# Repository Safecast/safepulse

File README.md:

# SafePulse

An open-source high-voltage power supply (HVPS) and pulse counter designed for Geiger tubes. The Safepulse is utilized in the newest version of Safecast devices, the [bGeigieZen](https://bgeigiezen.safecast.jp) and can be bough directly at [https://bgeigiezen.safecast.jp/store-2/safepulse/](https://bgeigiezen.safecast.jp/store-2/safepulse/)

---

## Table of Contents

- [Overview](#overview)
- [History](#history)
- [Features](#features)
- [Getting Started](#getting-started)
  - [Prerequisites](#prerequisites)
  - [Installation](#installation)
- [Documentation](#documentation)
- [Contributing](#contributing)
- [Issues and Support](#issues-and-support)
- [License](#license)

---

## Overview

SafePulse is a project aimed at creating a fully open-source high-voltage power supply that is compact, efficient, and reliable. Designed specifically for Geiger counters, it facilitates accurate radiation detection and measurement.

---

## History

The SafePulse journey began with Safecast's need for a high-performance HVPS that exceeded existing market solutions. Dan Sythe of International Medcom played a pivotal role in guiding the development process, providing components like the iRover—a commercial-grade miniature HVPS recognized by the IAEA.

While the iRover set a benchmark for reliability and performance, SafePulse was developed to customize its needs to the varying requirements of numerous Safecast device types. Using an open-source design based on a HEX CMOS inverter oscillator, MOSFET switch, and Cockroft-Walton multiplier, the initial design achieved low power consumption (80 µA). However, challenges such as double pulses to the CPU and high count rate predictability led to refinements, including adding a multivibrator for fixed pulse widths. SafePulse is as much a reference design as a specific product, as variants of the core SafePulse design already feature a high-speed nano-amp I2C counter as well as alternative packagings.

SafePulse evolved into a compact 4-layer design to meet size constraints while ensuring consistent performance across component substitutions.

---

## Features

- **Open-Source Design**: All design files and source code are publicly available for modification.
- **High Performance**: Provides reliable high-voltage output tailored for Geiger tubes.
- **Compact and Efficient**: Space-saving design with minimal power consumption.

---

## Getting Started

### Prerequisites

To work with SafePulse, ensure you have the following tools and components:

- [KiCad](https://www.kicad.org/): Open-source electronic design automation software.
- Electronic components listed in the project's bill of materials (BOM).

### Installation

1. **Clone the Repository**:
```

git clone https://github.com/Safecast/safepulse.git

```

2. **Open with KiCad**:
- Launch KiCad.
- Open the `SafePulse.kicad_pro` project file from the cloned repository.

3. **Review and Modify**:
- Access schematics and PCB layouts.
- Make desired modifications or improvements.

---

## Documentation

Detailed schematics and design documents are available in the repository. Refer to the [SafePulse.pdf](https://github.com/Safecast/safepulse/blob/main/SafePulse.pdf) file for comprehensive information.

---

## Contributing

Contributions are welcome! Follow these steps:

1. Fork the repository.
2. Create a new branch for your feature or bug fix:
```

git checkout -b feature-name

```
3. Commit your changes:
```

git commit -m "Add feature"

```
4. Push to your forked repository:
```

git push origin feature-name

```
5. Submit a pull request detailing your changes.

Please ensure contributions align with project objectives and coding standards.

---

## Issues and Support

For issues or questions, visit the [GitHub Issues](https://github.com/Safecast/safepulse/issues) section of the repository.

---

## License

This project is licensed under the MIT License. You are free to use, modify, and distribute this software under its terms.
```

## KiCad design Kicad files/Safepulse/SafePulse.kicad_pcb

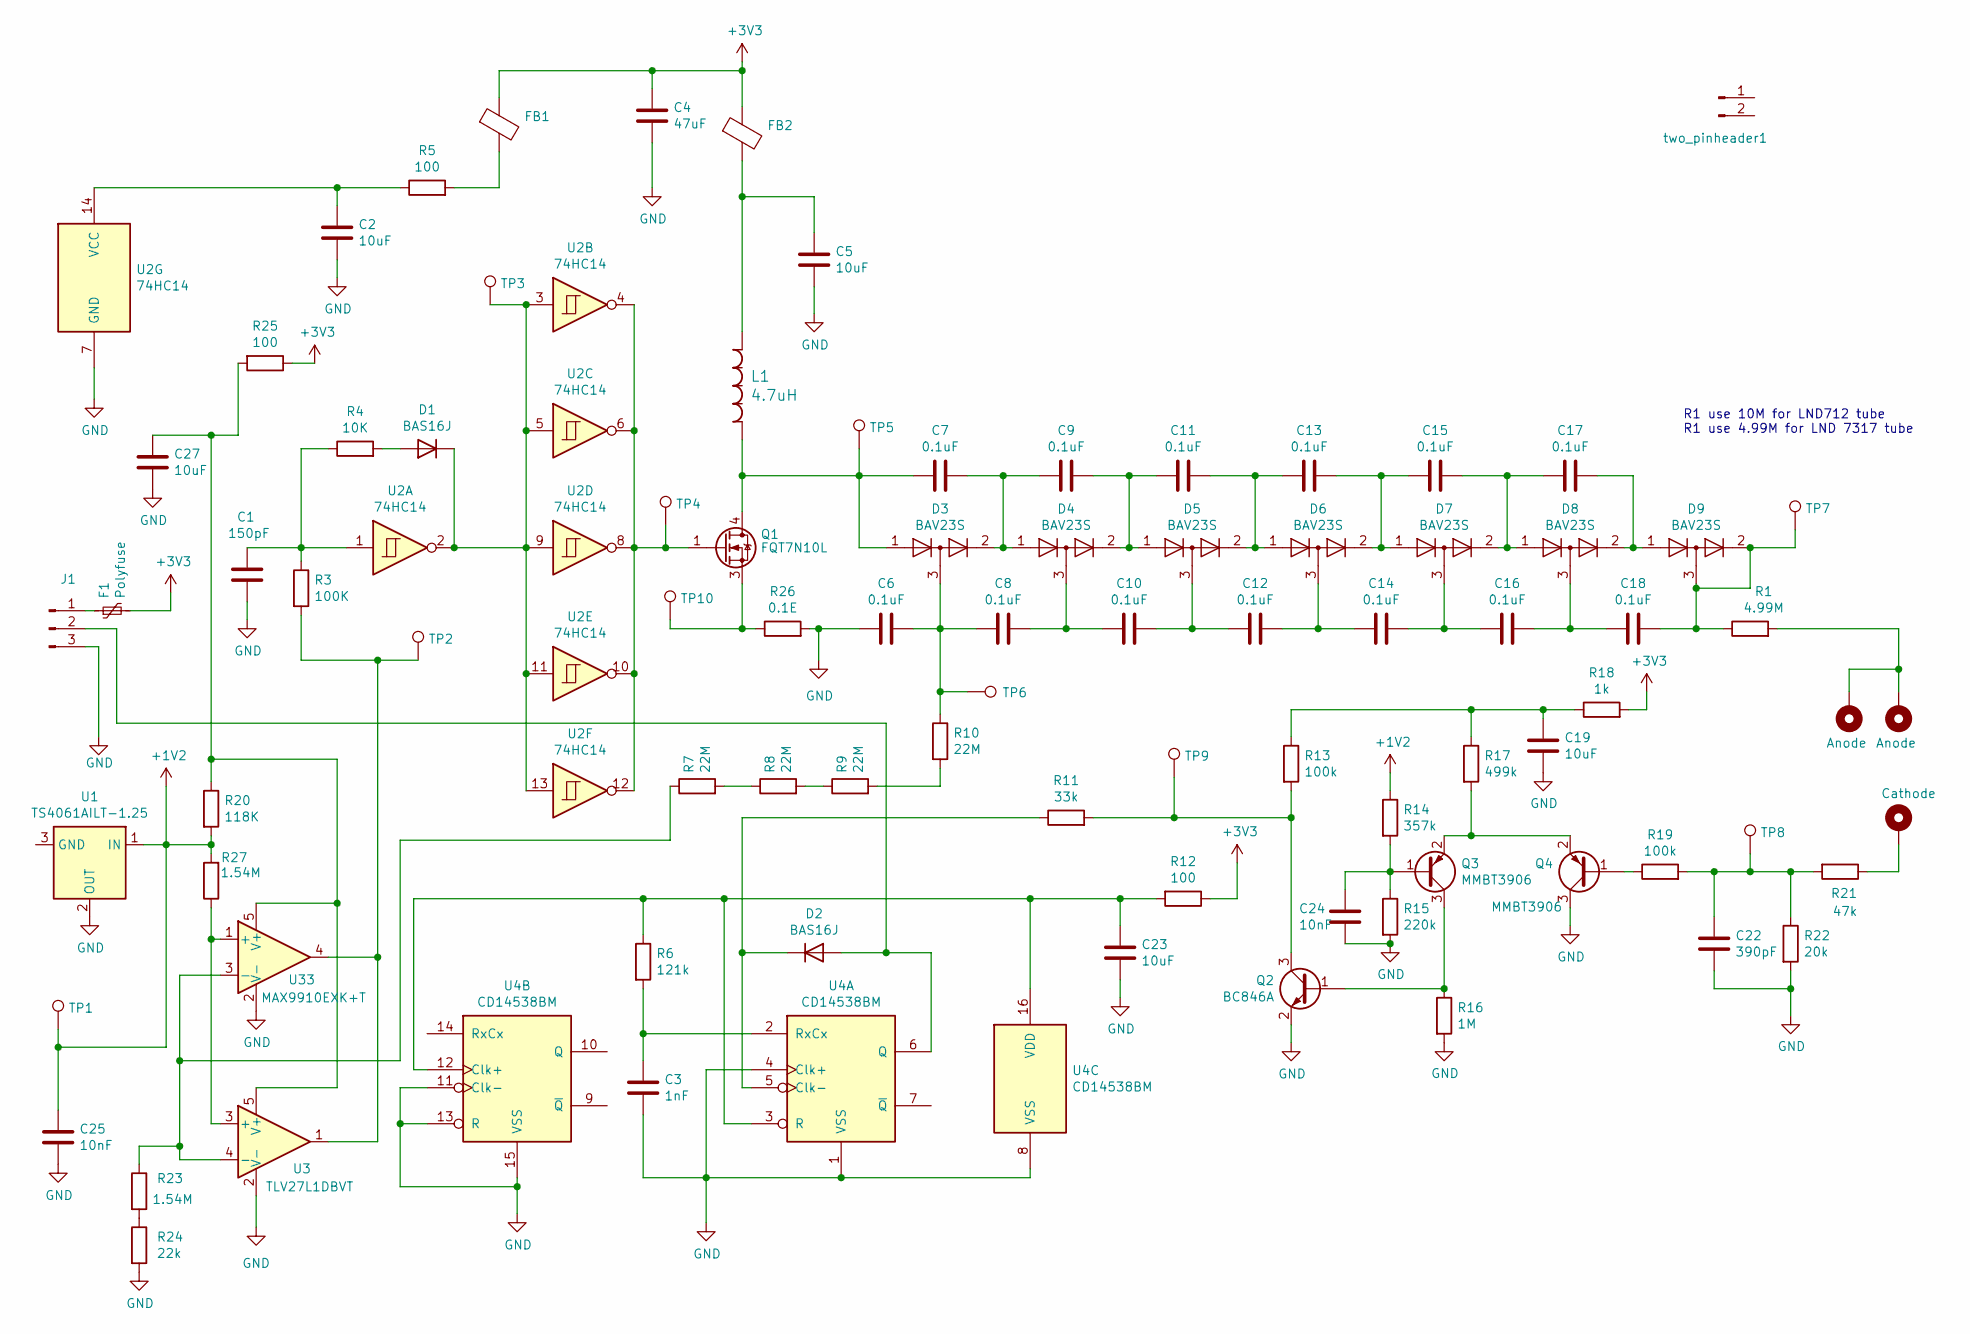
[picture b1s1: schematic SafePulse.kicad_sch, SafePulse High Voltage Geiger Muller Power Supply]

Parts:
C1: 150pF; C_0805_2012Metric; Digikey 732-12190-1-ND
C2, C5, C19, C23, C27: 10uF; C_0805_2012Metric; Digikey 1276-6455-1-ND
C3: 1nF; C_0805_2012Metric; Digikey 478-1371-1-ND
C4: 47uF; C_1210_3225Metric; Digikey 587-5425-1-ND
C6, C7, C8, C9, C10, C11, C12, C13, C14, C15, C16, C17, C18: 0.1uF; C_0805_2012Metric; Digikey 445-6808-1-ND
C22: 390pF; C_0805_2012Metric; Digikey 399-1132-1-ND
C24, C25: 10nF; C_0805_2012Metric; Digikey 1276-1015-1-ND
D1, D2: BAS16J; D_SOD-323; Digikey 1727-4797-1-ND
D3, D4, D5, D6, D7, D8, D9: BAV23S; SOT-23; Digikey BAV23SFSCT-ND
F1: Polyfuse; R_0805_2012Metric; Digikey 490-8510-1-ND
FB1, FB2: 74279220321; R_0805_2012Metric; Digikey 732-6125-1-ND
H1: Cathode; TestPoint_Loop_D2.60mm_Drill1.4mm_Beaded
H2, H4: Anode; TestPoint_Loop_D3.50mm_Drill1.4mm_Beaded
J1: Conn_01x03_Male; PinHeader_1x03_P2.54mm_Vertical
L1: 4.7uH; L_Taiyo-Yuden_MD-4040; Digikey 587-4451-1-ND
Q1: FQT7N10L; SOT-223-3_TabPin4; Digikey FQT7N10LTFCT-ND
Q2: BC846A; SOT-23; Digikey BC846A-7FDICT-ND
Q3, Q4: MMBT3906; SOT-23; Digikey MMBT3906LT1GOSCT-ND
R1: 4.99M; R_1206_3216Metric; Digikey RHM4.99MAICT-ND
R3: 100K; R_0805_2012Metric; Digikey RMCF0805FT100KCT-ND
R4: 10K; R_0805_2012Metric; Digikey RNCP0805FTD10K0CT-ND
R5: 100; R_0805_2012Metric; LCSC Part # C328380
R6: 121k; R_0805_2012Metric; Digikey 2019-RK73H2ATTD1213FCT-ND
R7, R8, R9, R10: 22M; R_0805_2012Metric; Digikey RMCF0805FT22M0CT-ND
R11: 33k; R_0805_2012Metric; Digikey A129767CT-ND
R12, R25: 100; R_0805_2012Metric; Digikey A106053CT-ND
R13, R19: 100k; R_0805_2012Metric; Digikey RMCF0805FT100KCT-ND
R14: 357k; R_0805_2012Metric; Digikey 2019-RK73H2ATTD3573FCT-ND
R15: 220k; R_0805_2012Metric; Digikey CR0805-FX-2203ELFCT-ND
R16: 1M; R_0805_2012Metric; Digikey YAG3361CT-ND
R17: 499k; R_0805_2012Metric; Digikey RMCF0805FT499KCT-ND
R18: 1k; R_0805_2012Metric; Digikey RNCP0805FTD1K00CT-ND
R20: 118K; R_0805_2012Metric; Digikey 311-118KCRCT-ND
R21: 47k; R_0805_2012Metric; Digikey 311-47.0KCRCT-ND
R22: 20k; R_0805_2012Metric; Digikey RMCF0805FT20K0CT-ND
R23, R27: 1.54M; R_0805_2012Metric; Digikey 311-1.54MCRCT-ND
R24: 22k; R_0805_2012Metric; Digikey CR0805-FX-2202ELFCT-ND
R26: 0.1E; R_0805_2012Metric; Digikey 408-1556-1-ND
TP1, TP2, TP3, TP4, TP5, TP6, TP7, TP8, TP9, TP10: TestPoint; TestPoint_Pad_1.0x1.0mm
U1: TS4061AILT-1.25; SOT-23; Digikey 497-15222-1-ND
U2: 74HC14; SOIC-14_3.9x8.7mm_P1.27mm; LCSC Part # C232776
U3: TLV27L1DBVT; SOT-23-5; Digikey 296-26814-1-ND
U4: CD14538BM; SOIC-16_3.9x9.9mm_P1.27mm; Digikey 296-32849-5-ND
U33: MAX9910EXK+T; SOT-353_SC-70-5; Digikey MAX9910EXK+TCT-ND
two_pinheader1: Conn_01x03_Male; PinHeader_1x02_P2.54mm_Vertical

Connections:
+1V2: C25.1, R14.1, R20.2, R27.2, TP1.1, U1.1 (IN)
+3V3: C4.1, F1.2, FB1.1, FB2.1, R12.1, R18.2, R25.1
GND: C1.2, C2.2, C3.2, C4.2, C5.2, C6.1, C19.2, C22.2, C23.2, C24.2, C25.2, C27.2, J1.3, Q2.2 (E), Q4.3 (C), R15.2, R16.2, R22.2, R24.2, R26.2, U1.2 (OUT), U2.7 (GND), U3.2 (V-), U4.1 (VSS), U4.4 (Clk+), U4.8 (VSS), U4.11 (Clk-), U4.13 (R), U4.15 (VSS), U33.2 (V-)
unnamed: C1.1, R3.1, R4.1, U2.1
unnamed: C5.1, FB2.2, L1.1
unnamed: C6.2, C8.1, D3.3 (K), R10.1, TP6.1
unnamed: C8.2, C10.1, D4.3 (K)
unnamed: C10.2, C12.1, D5.3 (K)
unnamed: C12.2, C14.1, D6.3 (K)
unnamed: C14.2, C16.1, D7.3 (K)
unnamed: C16.2, C18.1, D8.3 (K)
unnamed: C19.1, R13.1, R17.1, R18.1
unnamed: C22.1, R19.2, R21.2, R22.1, TP8.1
unnamed: D1.2 (A), R4.2
unnamed: D1.1 (K), TP3.1, U2.2, U2.3, U2.5, U2.9, U2.11, U2.13
unnamed: D2.2 (A), J1.2, U4.6 (Q)
unnamed: D2.1 (K), R11.1, U4.5 (Clk-)
unnamed: C7.2, C9.1, D3.2 (A), D4.1 (K)
unnamed: C9.2, C11.1, D4.2 (A), D5.1 (K)
unnamed: C11.2, C13.1, D5.2 (A), D6.1 (K)
unnamed: C13.2, C15.1, D6.2 (A), D7.1 (K)
unnamed: C15.2, C17.1, D7.2 (A), D8.1 (K)
unnamed: C17.2, D8.2 (A), D9.1 (K)
unnamed: C18.2, D9.2 (A), D9.3 (K), R1.1, TP7.1
unnamed: FB1.2, R5.2
unnamed: H1.1, R21.1
unnamed: H2.1, H4.1, R1.2
unnamed: F1.1, J1.1
unnamed: C7.1, D3.1 (K), L1.2, Q1.4 (D), TP5.1
unnamed: Q1.1 (G), TP4.1, U2.4, U2.6, U2.8, U2.10, U2.12
unnamed: Q1.3 (S), R26.1, TP10.1
unnamed: Q2.1 (B), Q3.3 (C), R16.1
unnamed: Q2.3 (C), R11.2, R13.2, TP9.1
unnamed: C24.1, Q3.1 (B), R14.2, R15.1
unnamed: Q3.2 (E), Q4.2 (E), R17.2
unnamed: Q4.1 (B), R19.1
unnamed: R3.2, TP2.1, U3.1, U33.4
unnamed: R7.2, R8.1
unnamed: R8.2, R9.1
unnamed: R9.2, R10.2
unnamed: R23.2, R24.1
unnamed: C2.1, R5.1, U2.14 (VCC)
unnamed: R27.1, U3.3 (+), U33.1 (+)
unnamed: R7.1, R23.1, U3.4 (-), U33.3 (-)
unnamed: C27.1, R20.1, R25.2, U3.5 (V+), U33.5 (V+)
unnamed: C23.1, R6.1, R12.2, U4.3 (R), U4.12 (Clk+), U4.16 (VDD)
unnamed: C3.1, R6.2, U4.2 (RxCx)

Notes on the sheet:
R1 use 10M for LND712 tube R1 use 4.99M for LND 7317 tube

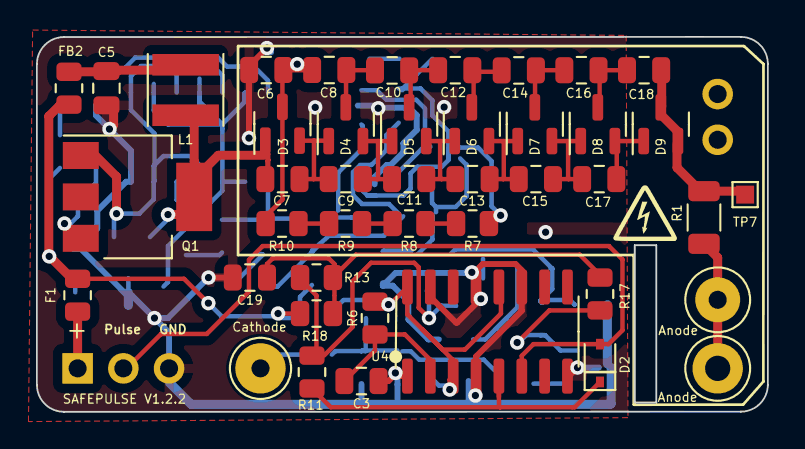
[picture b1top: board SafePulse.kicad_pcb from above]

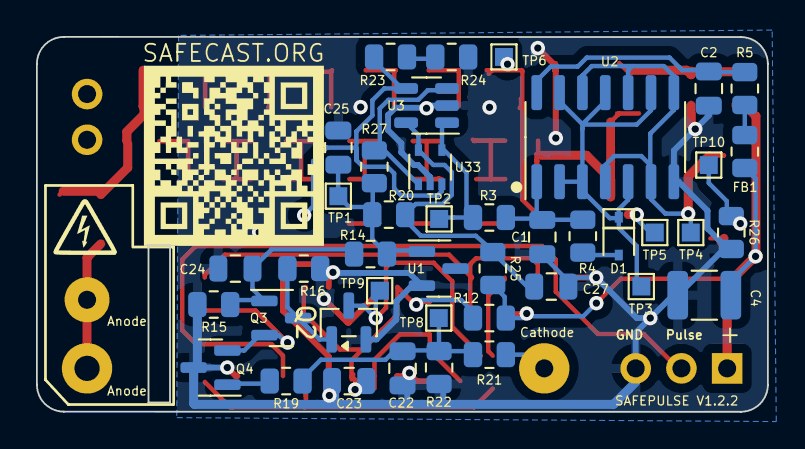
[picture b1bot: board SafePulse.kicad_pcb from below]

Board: 4 copper layers, 40.6 x 20.8 mm, 89 parts (43 on the bottom side), 47 nets.

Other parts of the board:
G2, G3: LOGO; HV warning

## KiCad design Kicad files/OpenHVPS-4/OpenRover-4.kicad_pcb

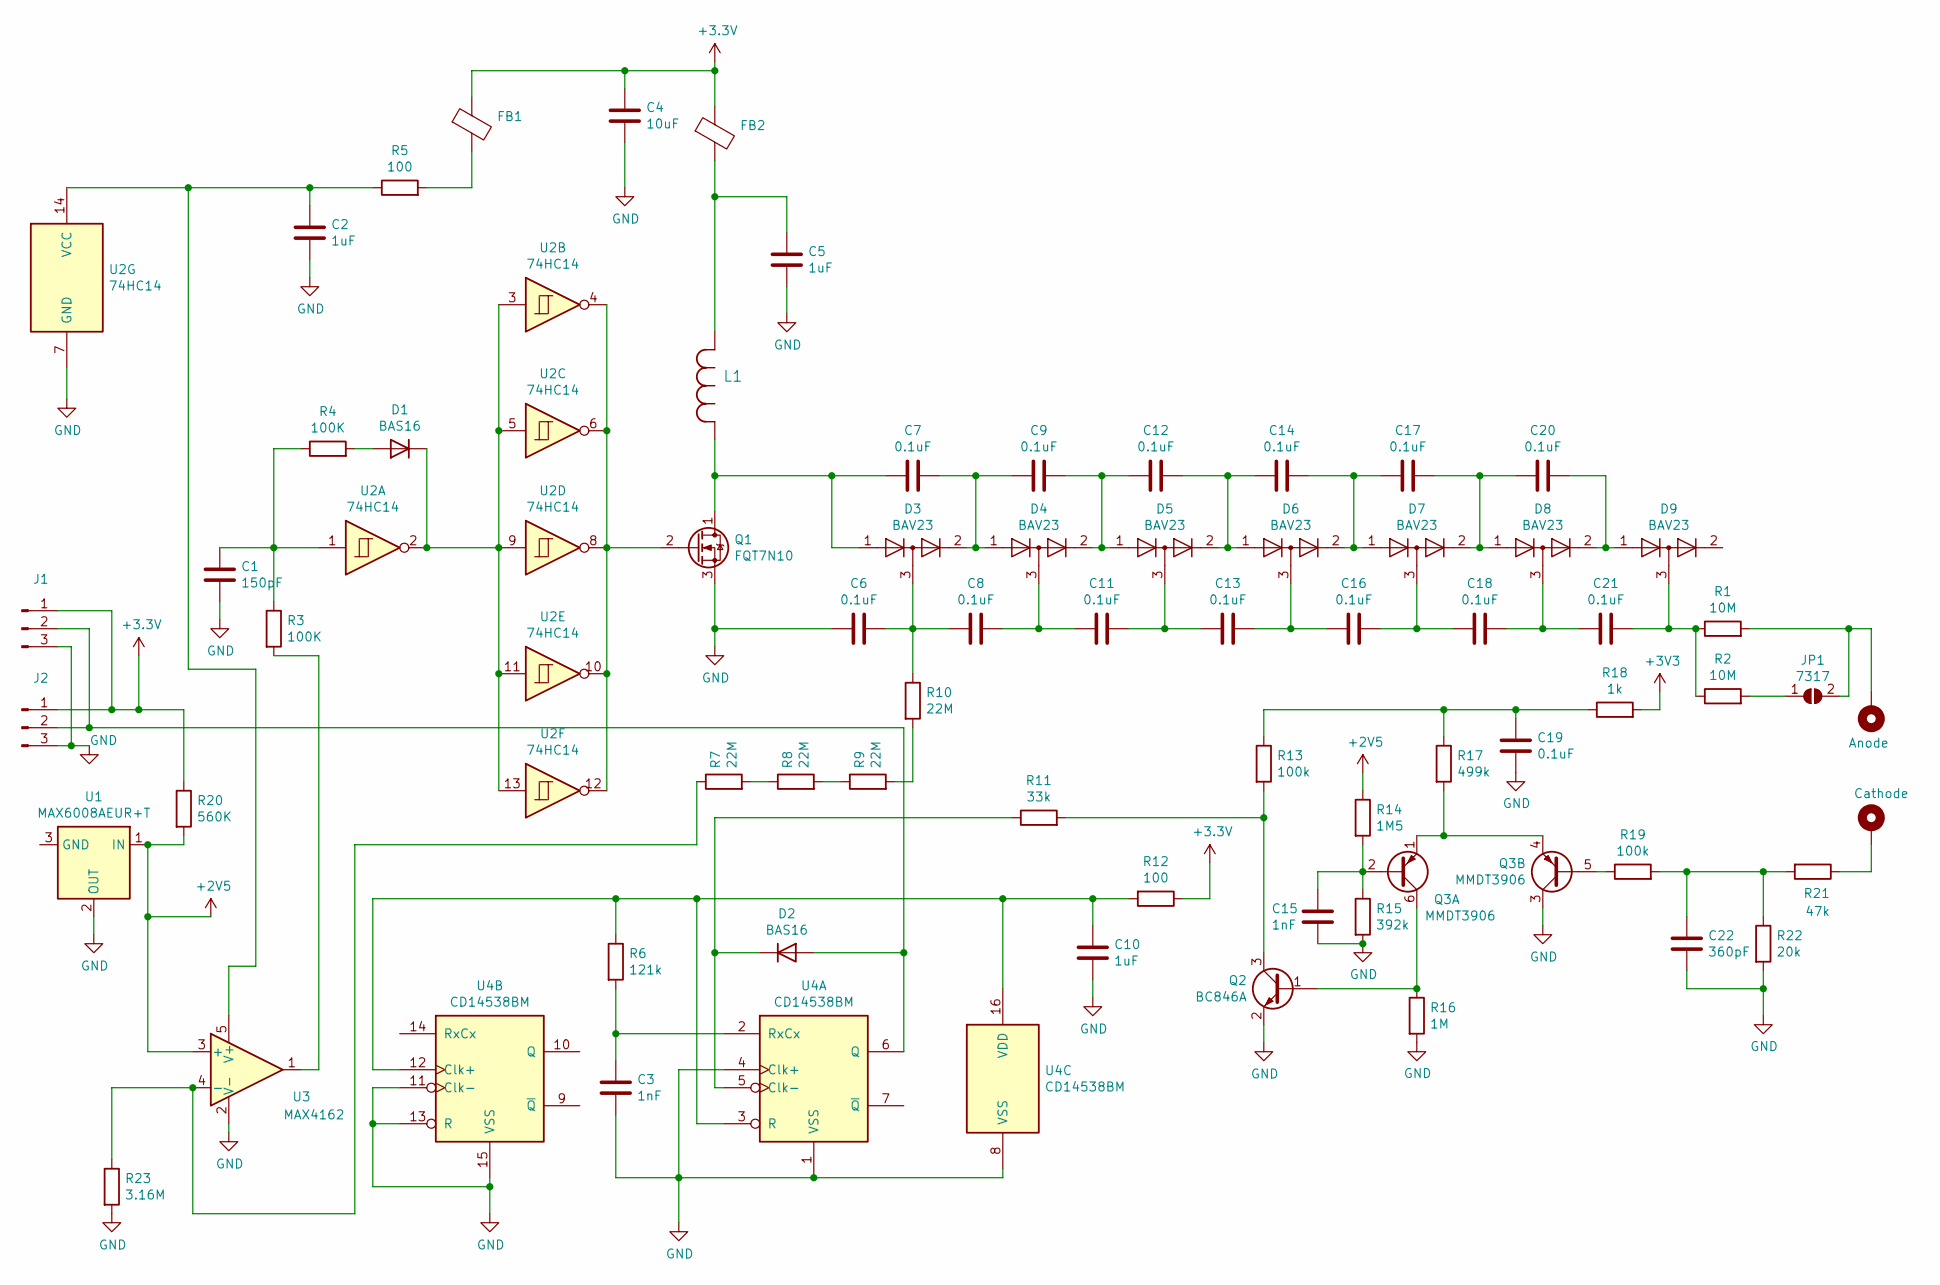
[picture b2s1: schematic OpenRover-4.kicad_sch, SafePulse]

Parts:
C1: 150pF; C_0805_2012Metric
C2, C5, C10: 1uF; C_0805_2012Metric
C3, C15: 1nF; C_0805_2012Metric
C4: 10uF; C_1210_3225Metric
C6, C7, C8, C9, C11, C12, C13, C14, C16, C17, C18, C19, C20, C21: 0.1uF; C_0805_2012Metric
C22: 360pF; C_0805_2012Metric
D1, D2: BAS16; D_SOT-23_ANK
D3, D4, D5, D6, D7, D8, D9: BAV23; SOT-23
FB1, FB2: BKP2125HS221-T; R_0805_2012Metric
H1: Cathode; TestPoint_Loop_D3.80mm_Drill2.0mm
H2: Anode; TestPoint_Loop_D3.80mm_Drill2.0mm
J1, J2: Conn_01x03_Male; PinHeader_1x03_P2.54mm_Vertical
JP1: 7317; SolderJumper-2_P1.3mm_Open_RoundedPad1.0x1.5mm
L1: NRS6020T2R2NMGJ; L_Taiyo-Yuden_MD-4040
Q1: FQT7N10; SOT-223-3_TabPin2
Q2: BC846A; SOT-23
Q3: MMDT3906; SOT-363_SC-70-6
R1, R2: 10M; R_1206_3216Metric
R3, R4: 100K; R_0805_2012Metric
R5, R12: 100; R_0805_2012Metric
R6: 121k; R_0805_2012Metric
R7, R8, R9, R10: 22M; R_0805_2012Metric
R11: 33k; R_0805_2012Metric
R13, R19: 100k; R_0805_2012Metric
R14: 1M5; R_0805_2012Metric
R15: 392k; R_0805_2012Metric
R16: 1M; R_0805_2012Metric
R17: 499k; R_0805_2012Metric
R18: 1k; R_0805_2012Metric
R20: 560K; R_0805_2012Metric
R21: 47k; R_0805_2012Metric
R22: 20k; R_0805_2012Metric
R23: 3.16M; R_0805_2012Metric
U1: MAX6008AEUR+T; SOT-23
U2: 74HC14; SOIC-14_3.9x8.7mm_P1.27mm
U3: MAX4162; SOT-23-5
U4: CD14538BM; SOIC-16_3.9x9.9mm_P1.27mm

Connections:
+2V5: R14.1, R20.2, U1.1 (IN), U3.3 (+)
GND: C1.2, C2.2, C3.2, C4.2, C5.2, C6.1, C10.2, C15.2, C19.2, C22.2, J1.3, J2.3, Q1.3 (S), Q2.2 (E), Q3.3 (C2), R15.2, R16.2, R22.2, R23.2, U1.2 (OUT), U2.7 (GND), U3.2 (V-), U4.1 (VSS), U4.4 (Clk+), U4.8 (VSS), U4.11 (Clk-), U4.13 (R), U4.15 (VSS)
unnamed: C1.1, R3.1, R4.1, U2.1
unnamed: C2.1, R5.1, U2.14 (VCC), U3.5 (V+)
unnamed: C3.1, R6.2, U4.2 (RxCx)
unnamed: C5.1, FB2.2, L1.1
unnamed: C6.2, C8.1, D3.3 (K), R10.1
unnamed: C7.1, D3.1 (K), L1.2, Q1.1 (D)
unnamed: C7.2, C9.1, D3.2 (A), D4.1 (K)
unnamed: C10.1, R6.1, R12.2, U4.3 (R), U4.12 (Clk+), U4.16 (VDD)
unnamed: C8.2, C11.1, D4.3 (K)
unnamed: C11.2, C13.1, D5.3 (K)
unnamed: C9.2, C12.1, D4.2 (A), D5.1 (K)
unnamed: C12.2, C14.1, D5.2 (A), D6.1 (K)
unnamed: C13.2, C16.1, D6.3 (K)
unnamed: C14.2, C17.1, D6.2 (A), D7.1 (K)
unnamed: C15.1, Q3.2 (B1), R14.2, R15.1
unnamed: C16.2, C18.1, D7.3 (K)
unnamed: C17.2, C20.1, D7.2 (A), D8.1 (K)
unnamed: C18.2, C21.1, D8.3 (K)
unnamed: C19.1, R13.1, R17.1, R18.1
unnamed: C20.2, D8.2 (A), D9.1 (K)
unnamed: C21.2, D9.3 (K), R1.1, R2.1
unnamed: C22.1, R19.2, R21.2, R22.1
unnamed: D1.1 (K), U2.2, U2.3, U2.5, U2.9, U2.11, U2.13
unnamed: D1.2 (A), R4.2
unnamed: D2.1 (K), R11.1, U4.5 (Clk-)
unnamed: D2.2 (A), J1.2, J2.2, U4.6 (Q)
unnamed: FB1.2, R5.2
unnamed: H1.1, R21.1
unnamed 30: H2.1, JP1.2 (B), R1.2; also elsewhere on the board
unnamed: JP1.1 (A), R2.2
unnamed: Q1.2 (G), U2.4, U2.6, U2.8, U2.10, U2.12
unnamed: Q2.1 (B), Q3.6 (C1), R16.1
unnamed: Q2.3 (C), R11.2, R13.2
unnamed: Q3.1 (E1), Q3.4 (E2), R17.2
unnamed: Q3.5 (B2), R19.1
unnamed: R3.2, U3.1
unnamed: R7.2, R8.1
unnamed: R8.2, R9.1
unnamed: R9.2, R10.2
unnamed: R7.1, R23.1, U3.4 (-)
no_connect_(D9-Pad2): D9.2 (A)
no_connect_(U1-Pad3): U1.3 (GND)
no_connect_(U4-Pad7): U4.7 (~Q)
no_connect_(U4-Pad9): U4.9 (~Q)
no_connect_(U4-Pad10): U4.10 (Q)
no_connect_(U4-Pad14): U4.14 (RxCx)

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
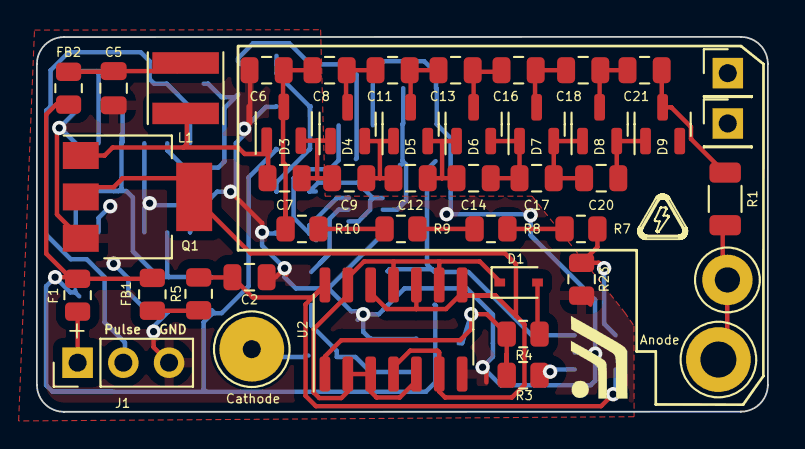
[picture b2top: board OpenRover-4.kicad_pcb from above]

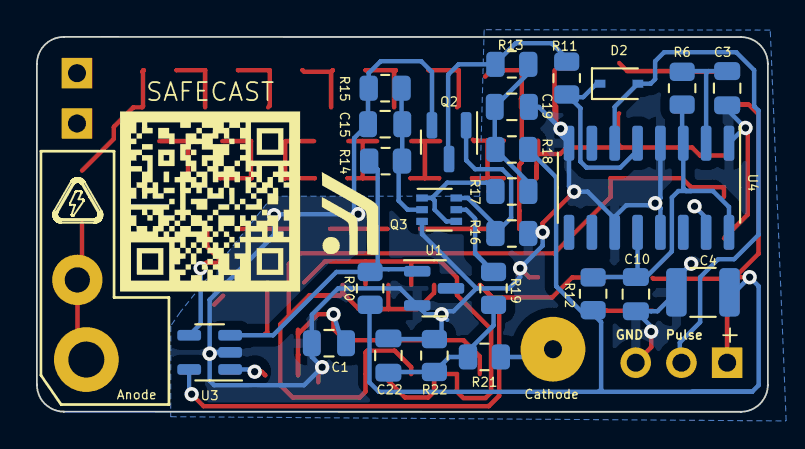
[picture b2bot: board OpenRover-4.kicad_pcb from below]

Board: 2 copper layers, 40.6 x 20.8 mm, 68 parts (26 on the bottom side), 43 nets.

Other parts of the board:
F1: Polyfuse; R_0805_2012Metric
H2#2: Anode; TestPoint_Loop_D3.80mm_Drill2.0mm

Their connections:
unnamed 30: H2#2.1; also elsewhere on the board

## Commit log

2021-01-09 Emply Kicad setup
2021-01-09 Added Irover 3D model files
2021-01-10 Updated with Allan his work.
2021-01-10 Modified read.me file
2021-01-10 Tested 74HC14 adding to the footprints
2021-01-10 Updated test for board sizes
2021-01-11 Add files via upload
    Finished front end.
2021-01-11 Updated the files from the allan zip files.
2021-01-11 Add files via upload
    Finished the Circuit Front End
2021-01-11 quick test parts layout/route and 3d models
2021-01-12 Renamed the files for OpenHVPS
2021-01-12 Create LICENSE
2021-01-12 Updated board with fill areas
2021-01-12 Tested new layout board
2021-01-12 Round conners and less vias. Space around holes
2021-01-12 version 2 of the SafePulse
2021-01-13 Added extra outputs and A-C placement moved
2021-01-13 test from allan
2021-01-13 test 4
2021-01-13 t test Q
2021-01-13 test rob allan
2021-01-13 test 7
2021-01-13 test8
2021-01-13 test 9
2021-01-13 cd \Users\allan\OneDrive\Documents\OpenHVPS Please enter the commit message for your changes. Lines starting updated the long board design
2021-01-13 changes to anode and cathode plus some parts layout, not routed!
2021-01-13 Cleaned up the tests
2021-01-14 Routed the board
2021-01-14 Changed foot prints for Anade/Cathode
2021-01-14 Replaced foot prints of anaode/cathode and text
2021-01-14 moved components around to shorten tracks, trying to keep layout critical stuff together
    Please enter the commit message for your changes. Lines starting
2021-01-14 Routed board.
2021-01-15 Added half version
2021-01-15 Moved components around and routed again.
2021-01-15 Moved terminal bloack away from HV
2021-01-15 small changes board layout and rerouted
2021-01-16 layout chnages
2021-01-16 Deleted zip file
2021-01-16 Updated files
2021-01-16 Updated all files
2021-01-16 Change the diodes
2021-01-16 Routed draft version
2021-01-16 One more rerout to cleanup.
2021-01-17 Sanity checks, parts shuffling, optimize copper pours
2021-01-17 updated board graphics
2021-01-17 Upadted lables
2021-01-17 BOM mostly done. cleaned up component labels
2021-01-17 Created BOM. updated component markings
2021-01-17 updated C22 value
2021-01-17 Adjusted text and changde sizes
2021-01-17 deleting local files to allow pull
2021-01-17 added hvps-2 dir
2021-01-17 Updated the BOM with clickable links
2021-01-17 Forgot the supply to the opamp - added. changed a capacitor value
2021-01-17 Added space at bottom and routed track +graphic.
2021-01-17 Cleaned up folders
2021-01-17 Fixed trace too close to Anode. flipped U3 to other side
2021-01-17 Added rays version
2021-01-17 Added Ray version
2021-01-18 fixed a couple of errors in BOM. reduced size of 2 diodes
2021-01-18 Added a fuse for reverse polarity protection
2021-01-18 Flipped R1 and +-P-GND and naming
2021-01-18 fixed corruption
2021-01-18 Made new branch
2021-01-18 Update new branch
2021-01-18 Fixed up
2021-01-18 Cleaned up more
2021-01-18 Updated board
2021-01-19 added latest chnages form Allan
2021-01-19 Corrected C22 value to 360pF updated BOM
2021-01-19 Update C22
2021-01-19 Updated C22 to 369pF
2021-01-19 Updated BOM clickable URL BOM
2021-01-19 XLSX formated BOM
2021-01-19 Generated gerber files
2021-01-20 added bom for PCBway and SEEED
2021-01-20 Changed D1 D2 added F1 and updated BOM
2021-01-20 Fixed DRC erros in layout, changed final BOM
2021-01-20 Moved some lables around
2021-01-21 Some more small adjustment of the graphics.
2021-01-21 Updated BOM fro SEEED
2021-01-23 Added logos
2021-01-23 Update the connectors sizes and two pin header
2021-01-23 New generated gerbers
2021-01-23 Fixed bom for Digikey
2021-01-23 Cleaned up old nameing of the repo
2021-01-24 Resetted head
2021-01-24 check for correct pushing.
2021-01-24 updated hazard logo
2021-01-24 Change graphic layout
2021-01-24 Moved TP7
2021-01-25 Adde Allan changes
2021-01-28 added schematic pdf and updated kicad files
2021-02-03 Updated BOM
2021-02-04 update url for C3,C15 for 0805
2021-02-05 Added B-mask SVG files for lasercutter stencil
2021-02-07 Changed R4 to 10K
2021-02-07 Cahnged numbering caps
2021-02-07 Updated BAV23S on schematic
2021-02-07 Updated references on PCB for disabling erros.
2021-02-08 Updated schematic fix Q1 pads
2021-02-08 Updated layout
2021-02-09 Cleaned up leftover traces
2021-02-09 fixed missing graphis and 3d model
2021-02-10 Updated the board to V1.1.
2021-02-10 Aligned more graphics and removed some via's
2021-02-10 updated board fixed via's DRC error.
2021-02-10 refilled ground plane.
2021-02-12 Changed Q3 package to single transitor. Now Q3+Q4
2021-02-12 added front and back pictures
2021-02-12 Removed TP1
2021-02-12 Removed TP1 from PCB
2021-02-17 Added cap for smoothing opamp
2021-02-17 Updated the date.
2021-02-17 updated text for model to avoid the via.
2021-02-17 Updated RC network around opamp and text changes.
2021-02-17 Updated with TP and some other small changes.
2021-02-18 Changed layout
2021-02-20 Chnaged R4 and C1 label placement
2021-02-21 Updated ground plane changed, capacitor to 47uF
2021-02-21 Moved some lables a bit to get them centered.
2021-02-24 added digikey bom from Allan and move U4 label
2021-03-02 Test
2021-03-24 Cahged pin sof U3 Max4162. V1.20.0
2021-03-29 Added test simulation
2021-04-11 Updated V1.2.0
2021-04-14 Added ground planes
2021-04-17 Safepulse V1.2.1
2021-04-26 Parts order for V1.2.1c
2021-05-11 V1.2.2
2021-05-12 updated board lables for V1.2.2.
2021-05-15 Added parts list for JLPCB
2021-05-16 Cleaned up V1.2.2
2021-05-16 Updated with Gerbers
2021-05-27 Garbage cleanup
2021-06-28 V1.2.3 with Qwiic and S-35770E01I-K8T2U
2021-06-28 Exported 3d models
2021-08-10 Updated schematic for I2C pulse counting
2021-08-11 Updated version number to v1.2.3
2021-08-19 V1.2.3 (allan)
2021-08-19 Fixed QR logo
2021-08-19 Added 3d models.
2021-08-20 Updated library for footprints
2021-08-22 Added Safepaulse V1.2.2. files
2021-08-22 Updated C1 and R24
2021-08-22 Updated Schematic and Board with new C1 and new R24 values
2021-08-22 Added the zipped gerbers for V1.2.2
2021-08-24 Updated csv
2021-09-03 Created postion files for pick&place
2021-10-23 Updated the files
2022-03-09 Checked out the files in thelatest version of Kicad Nightly.
2022-05-02 Updated C22 and R22 according to Joseph tests
2022-05-02 Updated version to V1.2.4
2022-05-02 Updated schematics with chnages of Joseph
2023-08-14 Added workspace
2024-04-04 Added Pulse maker
2024-04-04 Added pulsemaker again
2024-04-04 Updated Schematic and PCB
2024-04-04 Added production files fro JCL
2024-06-23 Updated with LCSC numbers
2024-06-24 Updated for JLC part numbers and stock
2024-06-29 added Allan changes
2024-06-29 Added VSCode workspace
2024-07-02 Updated BOM and position files for JLCPCB
2024-07-15 Updated V1.2.4 board with new JCLPCB number
2024-07-15 V1.2.5 boards
2024-07-16 Update layout for SOT-323 for U1 from a SOT-23 footprint
2025-04-02 Update README.md
    Reformating .
2025-04-02 Update README.md
    One more reformat
2025-04-02 Update README.md
    add I2C future plans
2025-04-03 V1.2.6 draft
2025-04-03 remove pictures from Allan
2025-04-03 Update README.md
    Added picture of the safepulse V1.2.5
2025-04-03 Update README.md
    Added link to the Zen in the README
2025-04-03 Updated production files
2025-04-03 cleaned up files
2025-04-04 Added QR code and updated files from Allan
2025-04-04 Added changes of Allan
2025-04-05 Aligned labels on board and replaces text labels in schematics
2025-04-05 Moved anode 01 inch..
2025-04-11 backup
2025-04-11 Updated V21.2.5 boards with C3 to 1.5nF
2025-04-11 Change C3 from 1.5nF to 1nF
2025-04-12 V1.2.6 with update BOM and C3 to 1nf
2025-04-12 V2.0.0
2025-04-14 Created branch for simulation
2025-04-14 Test simulation fixing issues
2025-04-18 Slowly progressing
2025-10-14 chore: remove backup zip files and update KiCad project settings
2025-10-25 Added workspace file
2025-10-25 Added fixes from Allan for the BOM and positions of the V1.2.2 file for JLCPCB
2025-10-30 Adde V22 url test
2025-10-30 Added V200 folder
2025-10-31 Added V2.0.0 boards
2025-10-31 Modified placement of labels and text
2025-10-31 Updated with Allan new files
2025-11-01 Update V2.0.0 boards and small labels moving around
2025-11-01 V2.0.0 updated files
2025-11-01 One more fix
2025-11-01 Some more graphics aligned.
2025-11-01 Put HV graphic back
2025-11-02 Cleaned up files . JLCPCB production files generated for V2.0.0
2025-11-12 Add initial production files for Safepulse project
    - Created BOM file with components and specifications.
    - Added designators for all components in designators.csv.
    - Generated netlist in IPC format for circuit connections.
    - Included positions of components in positions.csv for layout reference.
    - Created lock file for PCB design session.
2025-11-12 Update .gitignore to refine backup file exclusions and remove unnecessary patterns; update binary file for SafePulse High Voltage Geiger Muller Power Supply V1.2.2.
2025-11-17 Update README with purchase link for SafepulseAdde link to safepulse in store
    Added a link to purchase the Safepulse directly.
2026-01-20 Refactor code structure for improved readability and maintainability
